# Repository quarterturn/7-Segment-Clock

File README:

A 7-segment clock based on the ATMEGA 328p, MAX7219 led driver, a DS1307 RTC and some old HP calculator common-cathode bubble lens displays.

Clock features:
- displays time: hh.mm.ss A.
  if 12-hour, shows A or P
  if alarm set, shows . in the A/P position
- displays date: mm.dd.yy D
  shows the day of week 1-7 at D
- when the date display is selected, the time scrolls over while still keeping time to reveal the date, pauses, and then scrolls back
- during set mode, the selected value blinks
- allows for start/stop schedule for DST, as well as disabling DST conversion
- DST conversion also works during time set; if in DST, the time is converted back to STD for the RTC
- RTC stores time in STD local time
- alarm function allows none, weekends, weekdays and all days schedule

Includes free Nyan Cat alarm tune. Tunes are made with the miditones utility and played via the Playtune library.

Note that though there are three timers on the ATMEGA 328p we use timer0 for millis() so we limit Playtune polyphony to two notes.

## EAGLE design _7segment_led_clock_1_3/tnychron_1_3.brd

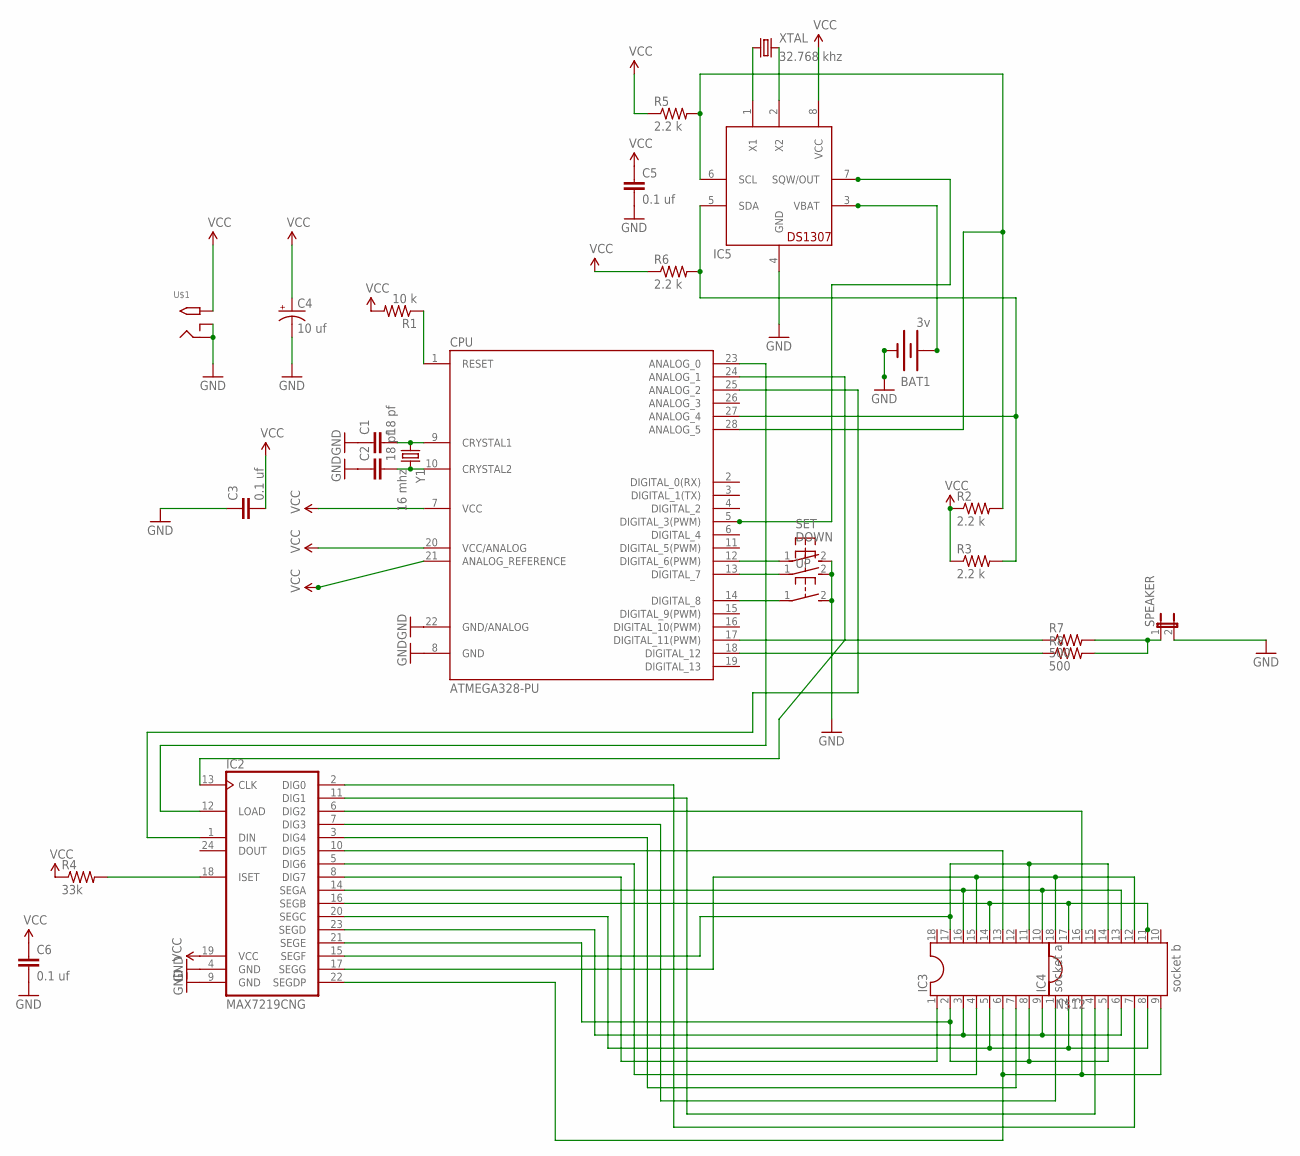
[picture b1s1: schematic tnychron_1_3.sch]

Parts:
BAT1: 3v; BATTCON_12MM_PTH
C1, C2: 18 pf; CAP-PTH-SMALL2
C3, C5, C6: 0.1 uf; CAP-PTH-SMALL2
C4: 10 uf; CPOL-RADIAL-10UF-25V
CPU: ATMEGA328-PU; DIL28-3
DOWN: 31-XX; B3F-31XX
IC2: MAX7219CNG; DIL24-3
IC3: socket a; DIL18
IC4: socket b; DIL18
IC5: DS1307; DIL08
R1: 10 k; AXIAL-0.4
R2, R3, R5, R6: 2.2 k; AXIAL-0.4
R4: 33k; AXIAL-0.4
R7, R8: 500; AXIAL-0.3
SET: 31-XX; B3F-31XX
SPEAKER: JUMPER-2PTH; 1X02
U$1: 2.1MMJACKTHM; PJ-102A
UP: 31-XX; B3F-31XX
XTAL: 32.768 khz; TC26H
Y1: 16 mhz; HC49US

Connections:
GND: BAT1.GND (-), C1.1, C2.1, C3.1, C4.2 (-), C5.2, C6.2, CPU.8 (GND), CPU.22 (GND/ANALOG), DOWN.2 (S), IC2.4 (GND), IC2.9 (GND), IC5.4 (GND), SET.2 (S), SPEAKER.2, U$1.RING, U$1.RING_SW, UP.2 (S)
unnamed: CPU.18 (DIGITAL_12), R8.P$1 (1)
unnamed: CPU.1 (RESET), R1.P$1 (1)
unnamed: C1.2, CPU.9 (CRYSTAL1), Y1.1
unnamed: C2.2, CPU.10 (CRYSTAL2), Y1.2
unnamed: IC2.2 (DIG0), IC4.7
unnamed: IC2.11 (DIG1), IC4.4
unnamed: CPU.28 (ANALOG_5), IC5.6 (SCL), R2.P$2 (2), R5.P$2 (2)
unnamed: CPU.27 (ANALOG_4), IC5.5 (SDA), R3.P$2 (2), R6.P$2 (2)
unnamed: CPU.5 (DIGITAL_3(PWM)), IC5.7 (SQW/OUT)
unnamed: CPU.17 (DIGITAL_11(PWM)), R7.P$1 (1)
unnamed: IC2.6 (DIG2), IC4.16
unnamed: IC2.7 (DIG3), IC4.1
unnamed: IC2.18 (ISET), R4.P$2 (2)
unnamed: IC2.3 (DIG4), IC3.7
unnamed: CPU.23 (ANALOG_0), IC2.12 (LOAD)
unnamed: CPU.24 (ANALOG_1), IC2.13 (CLK)
unnamed: CPU.25 (ANALOG_2), IC2.1 (DIN)
unnamed: IC2.10 (DIG5), IC3.13
unnamed: IC5.1 (X1), XTAL.1
unnamed: IC2.5 (DIG6), IC3.4
unnamed: IC2.8 (DIG7), IC3.1
unnamed: BAT1.VCC@1 (+), IC5.3 (VBAT)
unnamed: IC2.14 (SEGA), IC3.10, IC3.16, IC4.13
unnamed: IC2.16 (SEGB), IC3.14, IC4.11, IC4.17
unnamed: IC2.20 (SEGC), IC3.5, IC4.2, IC4.8
unnamed: IC2.23 (SEGD), IC3.3, IC3.9, IC4.6
unnamed: IC2.21 (SEGE), IC3.2, IC3.8, IC4.5
unnamed: CPU.12 (DIGITAL_6(PWM)), SET.1
unnamed: CPU.13 (DIGITAL_7), DOWN.1
unnamed: IC2.15 (SEGF), IC3.11, IC3.17, IC4.14
unnamed: IC2.17 (SEGG), IC3.15, IC4.12, IC4.18
unnamed: IC2.22 (SEGDP), IC3.6, IC4.3, IC4.9
unnamed: CPU.14 (DIGITAL_8), UP.1
unnamed: R7.P$2 (2), R8.P$2 (2), SPEAKER.1
unnamed: IC5.2 (X2), XTAL.2
VCC: C3.2, C4.1 (+), C5.1, C6.1, CPU.7 (VCC), CPU.20 (VCC/ANALOG), CPU.21 (ANALOG_REFERENCE), IC2.19 (VCC), IC5.8 (VCC), R1.P$2 (2), R2.P$1 (1), R3.P$1 (1), R4.P$1 (1), R5.P$1 (1), R6.P$1 (1), U$1.TIP

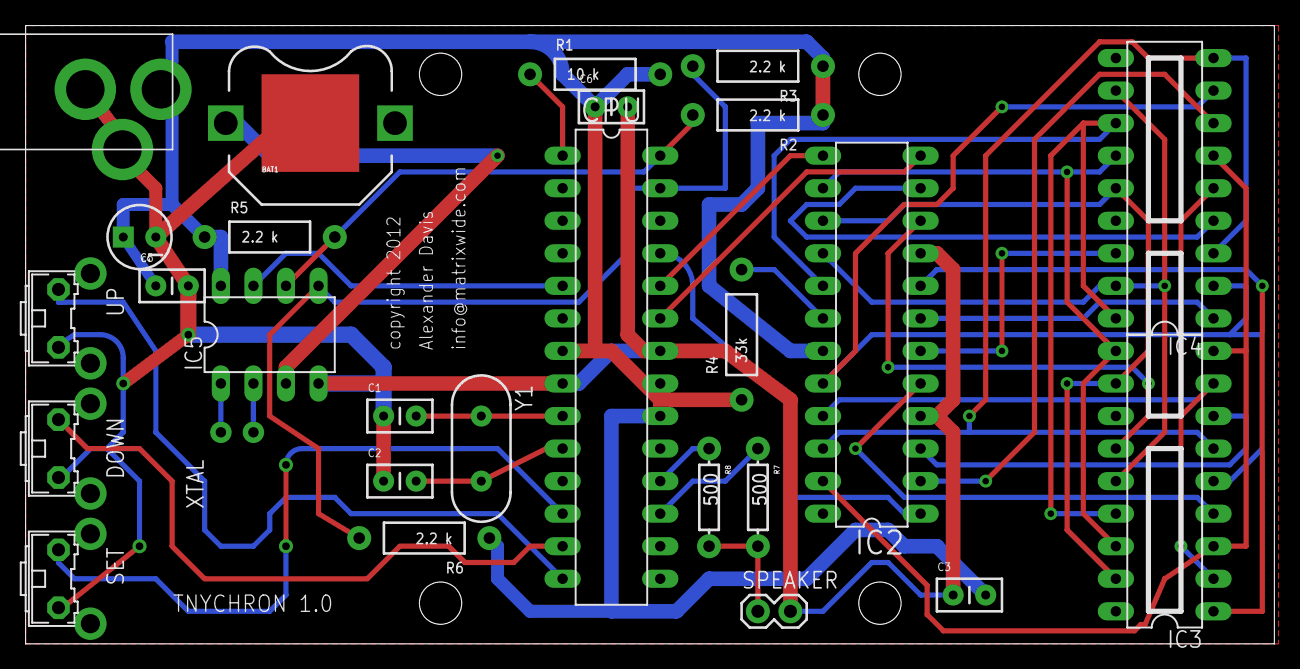
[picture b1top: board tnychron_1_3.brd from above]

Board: 2 copper layers, 97.5 x 48.2 mm, 31 parts (1 on the bottom side), 37 nets.

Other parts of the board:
U$4, U$5, U$6, U$7: STAND-OFF

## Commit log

2011-09-20 version 0.1
2011-09-20 Version 0.1 This code is under development. It does not compile. You have been warned.
2011-09-26 continued development
2011-10-01 Version 1.0 Tested and working
2011-10-01 Version 1.0 Tested and working.
2012-08-14 Tinychron 1.3 a complete LED digital clock
    based on:
    ATMEGA 328p micro
    DS1307 RTC
    MAX7219 LED display controller
    Uses these external libraries:
    Timelord
2012-08-14 Cleaned-up non-working versions
2012-12-31 software v 1.3 and Eagle CAD files
2012-12-31 software v 1.3, Eagle CAD files and Ardunio libraries
2013-01-22 v 1.4 bugfix for alarm minutes stored as alarmHr
2013-03-27 Version 1.5
2013-06-05 Version 1.5 added hex file

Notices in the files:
_7segment_led_clock_1_3/tnychron_1_3.brd:
copyright 2012
parts and their libraries:
SparkFun: Licensing: CC v3.0 Share-Alike You are welcome to use this library for commercial purposes.
